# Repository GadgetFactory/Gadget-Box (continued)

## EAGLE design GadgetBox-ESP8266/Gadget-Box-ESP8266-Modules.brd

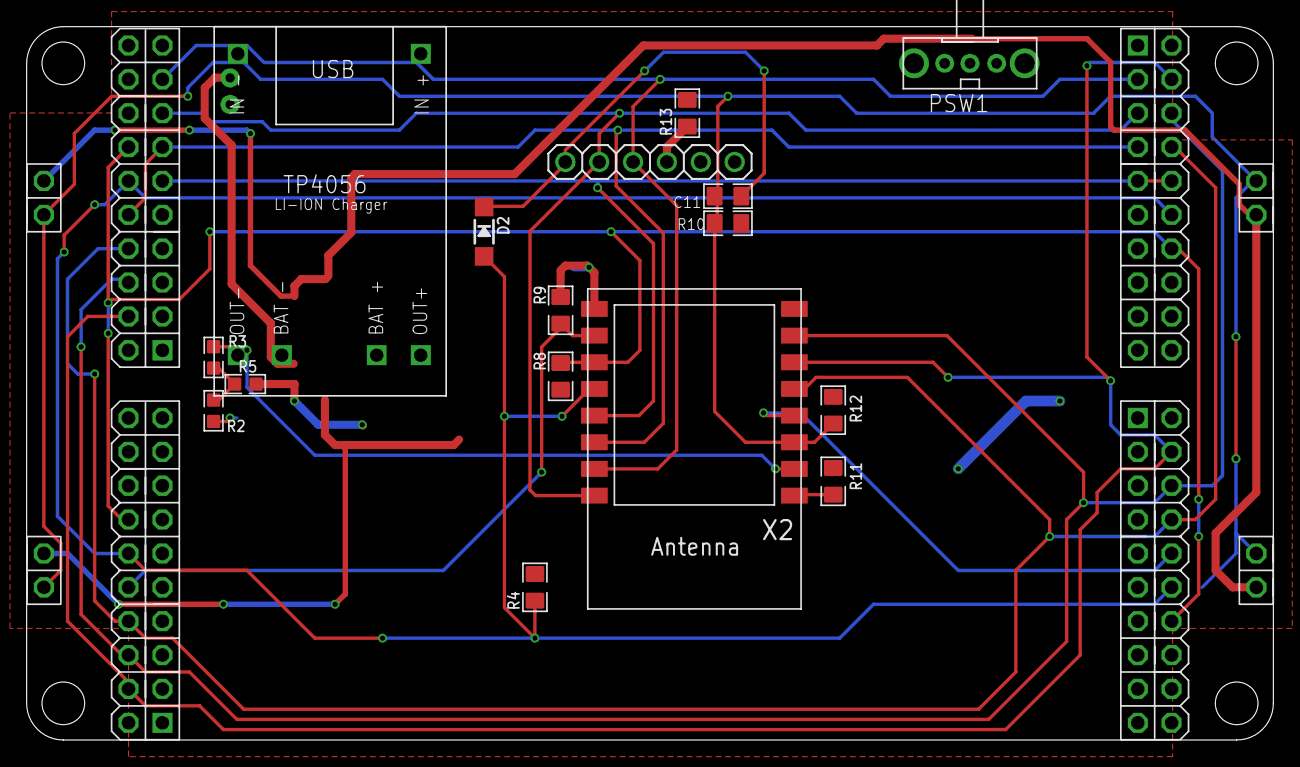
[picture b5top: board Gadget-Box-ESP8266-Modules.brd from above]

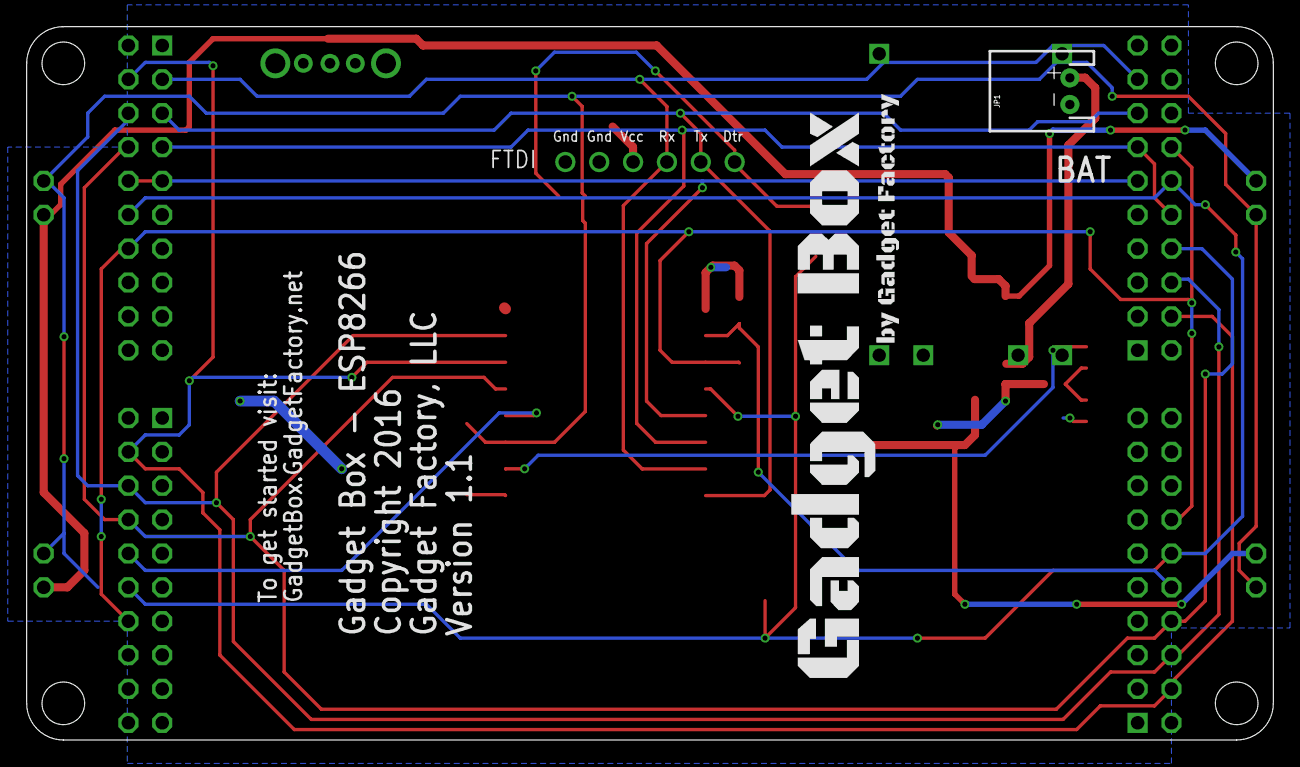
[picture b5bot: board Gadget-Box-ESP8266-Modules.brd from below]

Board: 2 copper layers, 93.5 x 53.5 mm, 23 parts (2 on the bottom side), 21 nets.

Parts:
$$U$1: ECOG93P53P5
AH: ECOGECOG_SLOT_ALT1; ECOG_ALT1
AL: ECOGECOG_SLOT_ALT1; ECOG_ALT1
BH: ECOGECOG_SLOT_ALT1; ECOG_ALT1
BL: ECOGECOG_SLOT_ALT1; ECOG_ALT1
C11: .1uF; 0805
D2: MBR120; SOD-123
FTDI: 1X06
JP1: JST-2-PTH-NS
PSW1: OS102011MA1Q
R2, R5: 100k; 0603
R3: DNP; 0603
R4, R8, R9, R10, R11, R12: 10K; 0805
R13: 0; 0805
U$1: TP4056
U$100: GADGETBOX_TEXT
X2: ESP-12

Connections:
3V3: AH.3V3@B8, AH.3V3@G8, AL.3V3@B8, AL.3V3@G8, BH.3V3@B8, BH.3V3@G8, BL.3V3@B8, BL.3V3@G8, R8.2, R10.2, R11.2, R12.2, R13.2, U$1.OUT+, X2.8
5V0: AH.5V@2, AL.5V@2, BH.5V@2, BL.5V@2
ADC: R3.1, X2.2
D0/RX/MISO: AL.G0, BH.G7, FTDI.3, X2.15
D1/TX/MOSI: AL.G1, BH.G6, FTDI.2, X2.16
D2: AL.G2, BH.G5, BH.SPI-CS@B3, X2.14
D3: AL.G3, AL.SPI-CS@B3, BH.G4, X2.13
DTR: C11.2, D2.C, FTDI.1
GND: AH.GND@B, AH.GND@G, AL.GND@B, AL.GND@G, BH.GND@B, BH.GND@G, BL.GND@B, BL.GND@G, FTDI.5, FTDI.6, JP1.1, R2.1, R9.1, U$1.BAT-, U$1.IN-, U$1.OUT-, X2.9
I2C-SCL: AH.I2C-SCL@B5, AL.I2C-SCL@B5, BH.I2C-SCL@B5, BL.I2C-SCL@B5, R8.1, X2.11
I2C-SDA/BOOTLOAD: AH.I2C-SDA@B4, AL.I2C-SDA@B4, BH.I2C-SDA@B4, BL.I2C-SDA@B4, D2.A, R4.1, X2.12
unnamed: R2.2, R3.2, R5.1
unnamed: FTDI.4, R13.1
RESET: AH.RESET@2, AL.RESET@2, BH.RESET@2, BL.RESET@2, C11.1, R10.1, R12.1, X2.3
RESET_NOTUSED: R11.1, X2.1
SPI-CSC: BL.SPI-CS@B3, R9.2, X2.10
SPI-CSD: AH.SPI-CS@B3, X2.4
SPI-MISO: AH.SPI-MISO@B0, AL.SPI-MISO@B0, BH.SPI-MISO@B0, BL.SPI-MISO@B0, X2.6
SPI-MOSI: AH.SPI-MOSI@B1, AL.SPI-MOSI@B1, BH.SPI-MOSI@B1, BL.SPI-MOSI@B1, X2.7
SPI-SCK: AH.SPI-SCK@B2, AL.SPI-SCK@B2, BH.SPI-SCK@B2, BL.SPI-SCK@B2, X2.5
VBAT: JP1.2, R5.2, U$1.BAT+
